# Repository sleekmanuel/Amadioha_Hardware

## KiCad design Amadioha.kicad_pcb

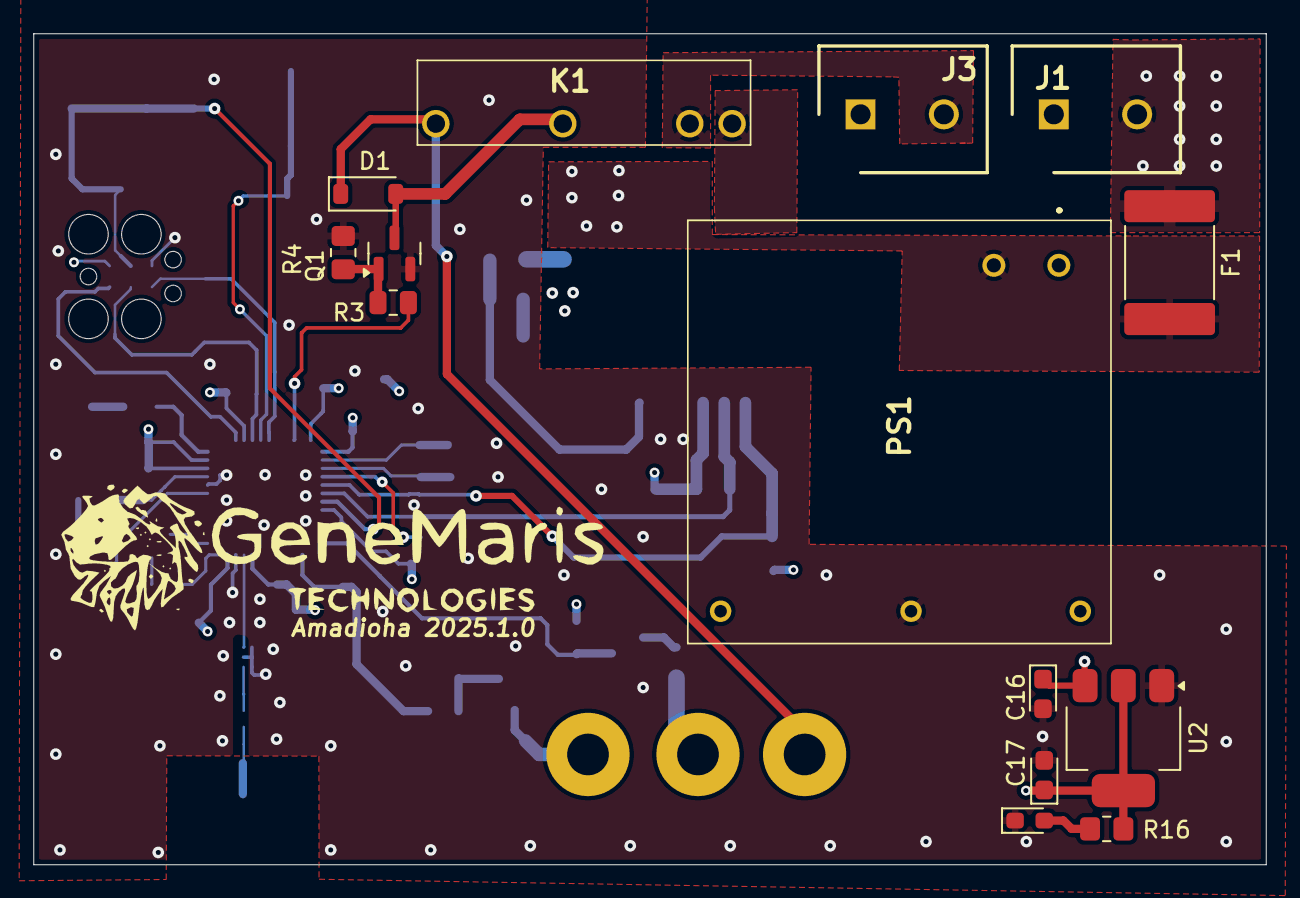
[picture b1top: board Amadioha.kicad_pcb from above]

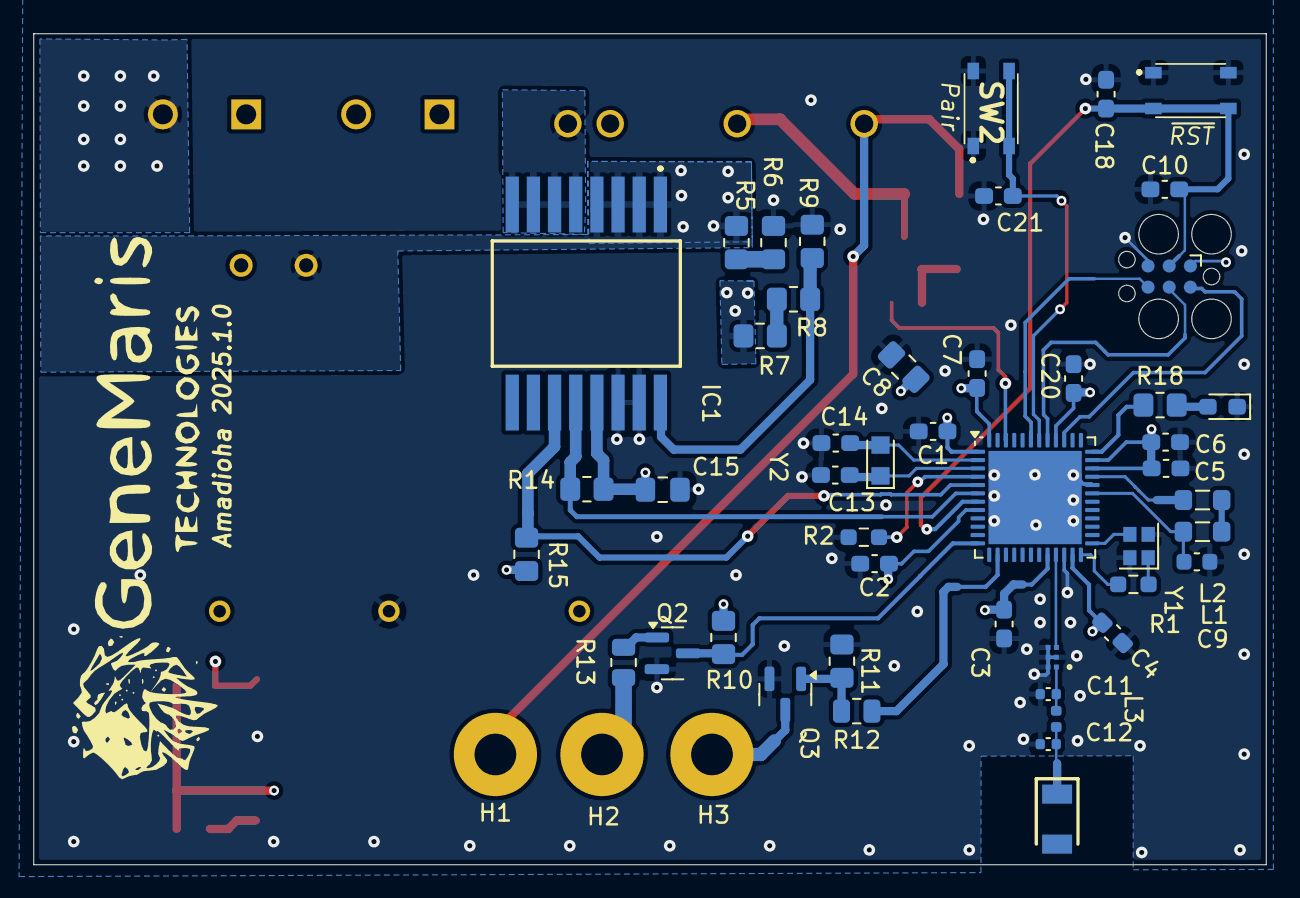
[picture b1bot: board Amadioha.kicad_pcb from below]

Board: 4 copper layers, 74.0 x 49.9 mm, 64 parts (50 on the bottom side), 42 nets.

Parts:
AE1: MLPF-WB55-01E3; MLPF-WB55-01E3_STM
AE2: AMCA31-2R450G-S1F-T3; ANTC3216X140N
C1, C2, C3, C4, C5, C6, C7, C10, C18, C20, C21: 0u1; C_0603_1608Metric_Pad1.08x0.95mm_HandSolder
C8: 4u7; C_0805_2012Metric_Pad1.18x1.45mm_HandSolder
C9: 4u7; C_0603_1608Metric
C11, C12: 1p2; C_0402_1005Metric
C13, C14: 10p; C_0603_1608Metric_Pad1.08x0.95mm_HandSolder
C15: 0u1; C_0805_2012Metric_Pad1.18x1.45mm_HandSolder
C16, C17: 10u; CP_EIA-2012-12_Kemet-R
D1: D_Schottky; D_SOD-123
D2: Green LED; LED_0603_1608Metric_Pad1.05x0.95mm_HandSolder
D3: Blue LED; LED_0603_1608Metric_Pad1.05x0.95mm_HandSolder
F1: Fuse; Fuse_2920_7451Metric
H1, H2, H3: MountingHole_Pad; MountingHole_2.5mm_Pad
IC1: ACS37800KMACTR-030B3-I2C; ACS37002LMCA050U5
J1, J3: 691137710002; SHDR2W70P0X500_1X2_1000X750X1160P
J2: SW_Debug; Tag-Connect_TC2030-IDC-FP_2x03_P1.27mm_Vertical
K1: G6DN-1A-SL_DC5; G6DN1ASLDC5
L1: 10n; L_0805_2012Metric_Pad1.05x1.20mm_HandSolder
L2: 10u; L_0805_2012Metric_Pad1.05x1.20mm_HandSolder
L3: 3n6; L_0402_1005Metric
PS1: ECE05US05
Q1, Q2, Q3: BSS138; SOT-23
R1: 0; R_0603_1608Metric_Pad0.98x0.95mm_HandSolder
R2: 10k; R_0603_1608Metric_Pad0.98x0.95mm_HandSolder
R3, R12, R13: 1k; R_0805_2012Metric
R4, R10, R11, R14, R15: 10k; R_0805_2012Metric_Pad1.20x1.40mm_HandSolder
R5, R6, R7, R8: 1M; R_0805_2012Metric_Pad1.20x1.40mm_HandSolder
R9: 100m; R_0805_2012Metric_Pad1.20x1.40mm_HandSolder
R16, R18: 220; R_0805_2012Metric_Pad1.20x1.40mm_HandSolder
SW1, SW2: PTS815; PTS815SJK250SMTRLFS
U1: STM32WB55CGU6; QFN-48-1EP_7x7mm_P0.5mm_EP5.6x5.6mm
U2: NCP1117-3.3_SOT223; SOT-223-3_TabPin2
Y1: 32MHz; Crystal_SMD_2016-4Pin_2.0x1.6mm
Y2: 32K768; Crystal_SMD_2012-2Pin_2.0x1.2mm_HandSoldering

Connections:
+3V3: C1.1, C2.1, C3.1, C4.1, C5.1, C6.1, C7.1, C8.1, C15.1, C17.1, C20.1, IC1.13 (VCC), J2.1 (VCC), R10.2, R14.2, R15.2, R16.1, U1.1 (VBAT), U1.8 (VDDA), U1.20 (VDD), U1.23 (VDDRF), U1.34 (VDDSMPS), U1.35 (VDD), U1.40 (VDDUSB), U1.48 (VDD), U2.2 (VO)
+5V: C16.1, D1.1 (K), H1.1, K1.8 (COM), PS1.5 (+VOUT), U2.3 (VI)
/AC_L: F1.1, J1.2
/AC_N: J1.1, J3.1, PS1.1 (AC(N)), R7.1
/HSE_IN: U1.25 (OSC_IN), Y1.3
/HSE_OUT: R1.2, U1.24 (OSC_OUT)
/IC1_IP+: F1.2, IC1.1 (IP+_1), IC1.2 (IP+_2), IC1.3 (IP+_3), IC1.4 (IP+_4), PS1.2 (AC(L)), R5.1
/IC1_IP-: IC1.5 (IP-_1), IC1.6 (IP-_2), IC1.7 (IP-_3), IC1.8 (IP-_4), K1.1 (COIL_1)
/IC1_SCL: IC1.11 (SCL_/_SCLK), R15.1, U1.5 (PB8)
/IC1_SDA: IC1.12 (SDA_/_MISO), R14.1, U1.6 (PB9)
/K1_C: D1.2 (A), K1.5 (NO), Q1.3 (D)
/K1_C2: J3.2, K1.2 (COIL_2)
/LOAD_EN: R3.1, U1.46 (PB6)
/Pair: C21.2, SW2.3 (K), SW2.4 (A), U1.42 (PA15)
/RF: AE1.A3 (IN), U1.21 (RF1)
/RF_ANT: AE2.1 (FEED), C12.1, L3.1
/RF_LP: AE1.A1 (OUT), C11.1, L3.2
/SMPSFB: C9.1, L2.1, U1.31 (VFBSMPS)
/SMPSLX: L1.2, U1.33 (VLXSMPS)
/SMPSLX2: L1.1, L2.2
/SWCLK: J2.4 (SWCLK), U1.41 (PA14)
/SWDIO: J2.2 (SWDIO), U1.39 (PA13)
/SWITCH_LED: R12.2, U1.14 (PA5)
/SWITCH_PB: Q2.3 (D), R10.1, U1.12 (PA3)
/SWO: J2.6 (SWO), U1.43 (PB3)
/~RST: C10.2, C18.2, J2.3 (~RESET), SW1.3 (K), SW1.4 (A), U1.7 (NRST)
GND: AE1.A2 (GND4), AE1.B1 (GND3), AE1.B2 (GND2), AE1.B3 (GND1), C1.2, C2.2, C3.2, C4.2, C5.2, C6.2, C7.2, C8.2, C9.2, C10.1, C11.2, C12.2, C13.2, C14.2, C15.2, C16.2, C17.2, C18.1, C20.2, C21.1, D2.1 (K), D3.1 (K), IC1.14 (GND), IC1.15 (VINN), J2.5 (GND), PS1.4 (-VOUT), Q1.2 (S), Q2.2 (S), Q3.2 (S), R2.2, R4.1, R6.2, R9.1, R11.1, SW1.1, SW1.2, SW2.1, SW2.2, U1.22 (VSSRF), U1.32 (VSSSMPS), U1.49 (VSS), U2.1 (GND), Y1.2, Y1.4
unnamed: D2.2 (A), R16.2
unnamed: D3.2 (A), R18.1
unnamed: H2.1, R13.1
unnamed: IC1.16 (VINP), R8.2, R9.2
unnamed: Q1.1 (G), R3.2, R4.2
unnamed: Q2.1 (G), R13.2
unnamed: H3.1, Q3.3 (D)
unnamed: Q3.1 (G), R11.2, R12.1
unnamed: R1.1, Y1.1
unnamed: R5.2, R6.1
unnamed: R7.2, R8.1
unnamed: R18.2, U1.36 (PA10)
unnamed: C14.1, U1.2 (PC14), Y2.2
unnamed: C13.1, U1.3 (PC15), Y2.1
unnamed: R2.1, U1.4 (PH3)

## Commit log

2025-12-17 PCB validation and manufacturing
2025-12-23 revision norm.
2025-12-26 i dont know
2025-12-30 trace width ajdustment
2026-01-08 1/7/2026
